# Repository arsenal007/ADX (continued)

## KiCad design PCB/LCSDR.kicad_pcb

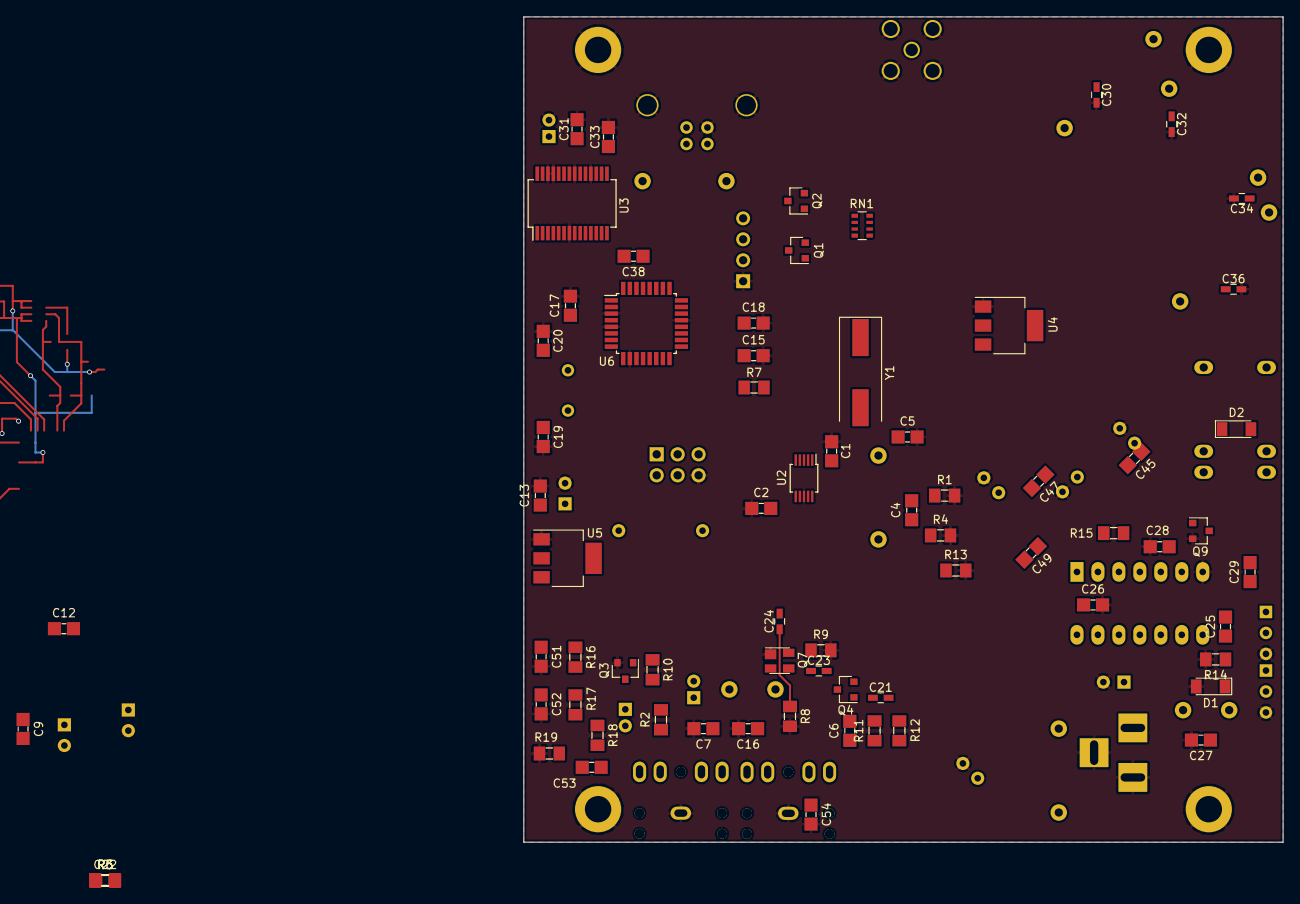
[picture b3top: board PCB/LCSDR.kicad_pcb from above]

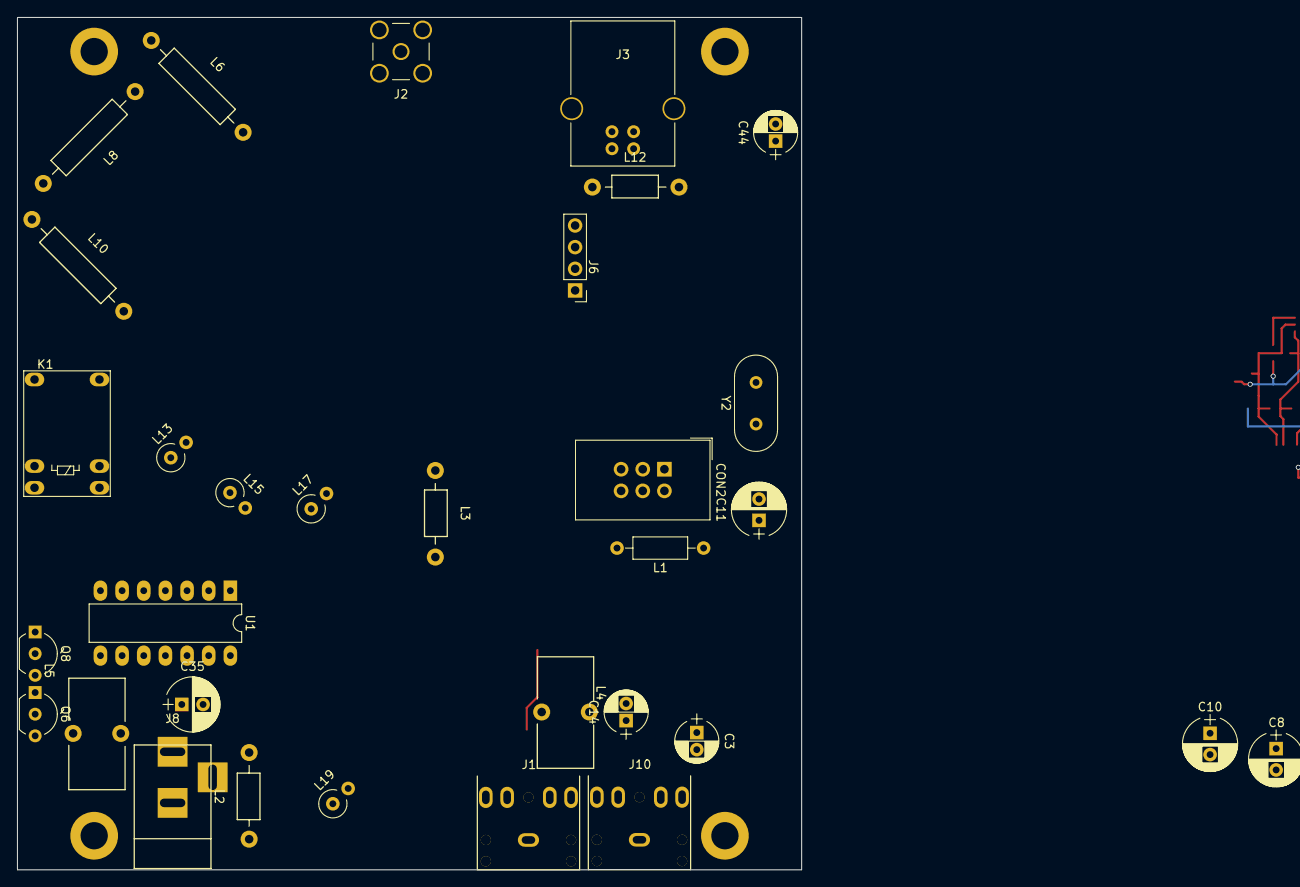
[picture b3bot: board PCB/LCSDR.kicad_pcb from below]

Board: 2 copper layers, 92.0 x 100.0 mm, 108 parts (32 on the bottom side), 61 nets.

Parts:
C1, C2: 1µF; C_1206_0603
C3, C14: 2.2uF; CP_Radial_D5.0mm_P2.00mm
C4, C5, C6, C7, C9, C12, C13, C15, C16, C17, C18, C22, C25, C26, C29, C31, C33, C38, C53, C54: 100nF; C_1206_0603
C8, C10, C11, C35: 100uF; CP_Radial_D6.3mm_P2.50mm
C19, C20: 22pF; C_1206_0603
C21, C23, C24: 10nF; C_0603_HandSoldering
C27, C28: 100pF; C_1206_0603
C30, C36: 270pF; C_0603_HandSoldering
C32, C34: 680pF; C_0603_HandSoldering
C44: 10uF; CP_Radial_D5.0mm_P2.00mm
C45, C49: 330pF; C_1206_0603
C47: 220pF; C_1206_0603
C51, C52: 10nF; C_1206_0603
CON2: AVR-ISP-6; IDC-Header_2x03_Pitch2.54mm_Straight
D1, D2: LL4148; D_MiniMELF
J1: MIC; audio_jack_3_5mm_PJ307
J2: ANT; SMA_THT_Jack_Straight
J3: USB_B
J6: I2C; Pin_Header_Straight_1x04_Pitch2.54mm
J8: Jack-DC; BARREL_JACK
J10: SPK; audio_jack_3_5mm_PJ307
J12, J13, J14, J15: Conn_01x01; MountingHole_3.2mm_M3_DIN965_Pad
K1: TIANBO-HJR-4102-L; Relay_SPDT_HJR-4102
L1: 100uH; R_Axial_DIN0207_L6.3mm_D2.5mm_P10.16mm_Horizontal
L2: 33µH; Choke_Horizontal_RM10mm
L3: 4.7uH; Choke_Horizontal_RM10mm
L4: 100mH; Choke_Toroid_6,5x13mm_Vertical
L5: 20uH; Choke_Toroid_6,5x13mm_Vertical
L6, L10: 1.32uH; Choke_Horizontal_RM15mm
L8: 1.72uH; Choke_Horizontal_RM15mm
L12: 10uH; Choke_Horizontal_RM10mm
L13, L19: 1uH; R_Axial_DIN0309_L9.0mm_D3.2mm_P2.54mm_Vertical
L15, L17: 680nH; R_Axial_DIN0309_L9.0mm_D3.2mm_P2.54mm_Vertical
Q1, Q2: 2N7002; SOT-23
Q3: BC847; SOT-23
Q4: BFR93A; SOT-23
Q6, Q8: BS170; TO-92_Inline_Wide
Q7: BF998; SOT-143
Q9: BC849; SOT-23
R1: 4R7; R_1206_0603
R2: 3.9K; R_1206_0603
R3, R5: 100; R_1206_0603
R4: 47R; R_1206_0603
R6: 2.2k; R_1206_0603
R7, R16, R17: 10k; R_1206_0603
R8, R12: 470; R_1206_0603
R9: 27k; R_1206_0603
R10: 470k; R_1206_0603
R11: 2.7k; R_1206_0603
R13: 1k; R_1206_0603
R14: 2.7K; R_1206_0603
R15: 3.3k; R_1206_0603
R18: 1M; R_1206_0603
R19: 4.7K; R_1206_0603
RN1: 10k; R_Array_Convex_4x0603
U1: 74AC14; DIP-14_W7.62mm_LongPads
U2: Si5351; MSOP-10_3x3mm_Pitch0.5mm
U3: FT232RL; SSOP-28_5.3x10.2mm_Pitch0.65mm
U4: LM1117-5.0; SOT-223-3_TabPin2
U5: LM1117-3.3; SOT-223-3_TabPin2
U6: ATMEGA328P-AU; TQFP-32_7x7mm_Pitch0.8mm
Y1: 25Mhz; Crystal_SMD_HC49-SD
Y2: 20Mhz; Crystal_HC49-U_Vertical

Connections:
+3V3: C1.1, C11.1, C13.1, L1.1, Q1.1, Q2.1, R18.1, RN1.5, RN1.6, U2.1, U5.2
+5V: C10.1, C12.1, C15.1, C17.1, C26.1, CON2.2, J6.2, L12.1, R7.1, RN1.7, RN1.8, U1.14, U4.2, U5.3, U6.4, U6.6, U6.18
+12V: C8.1, C9.1, D2.1, K1.8, L2.1, R2.1, R3.2, R5.2, U4.3
+12VA: C35.1, J8.1, L2.2, L5.1
CLK1: C24.2, U2.9
CLK2: U1.1, U1.3, U1.5, U1.9, U1.11, U1.13, U2.6
GND: C1.2, C2.1, C5.2, C7.2, C8.2, C9.2, C10.2, C11.2, C12.2, C13.2, C15.2, C16.2, C17.2, C18.2, C19.2, C20.2, C22.2, C26.2, C27.2, C28.2, C30.2, C31.2, C32.2, C33.2, C34.2, C35.2, C36.2, C44.2, C51.2, C52.2, C54.2, CON2.6, D1.2, J1.1, J2.2, J3.4, J3.5, J6.1, J8.2, J8.3, J10.1, J12.1, J13.1, J14.1, J15.1, L13.2, L15.2, L17.2, L19.2, Q3.2, Q6.3, Q7.1, Q8.3, Q9.2, R1.2, R4.2, R8.2, R9.2, R13.2, R14.2, R19.2, U1.7, U2.8, U3.7, U3.18, U3.21, U3.25, U3.26, U4.1, U5.1, U6.3, U6.5, U6.10, U6.21
IO_5: U6.1, U6.2
LPF: C36.1, K1.1, K1.12, L10.2
unnamed: C2.2, L1.2, U2.7
unnamed: C3.1, Q3.3, R2.2, R10.2
unnamed: C3.2, C54.1, J1.2, J1.3, J1.4, J1.5
unnamed: C4.1, Q4.2, R4.1
unnamed: C4.2, R1.1
unnamed: C5.1, L3.1, R3.1
unnamed: C6.1, R11.1, R12.1
unnamed: C7.1, C14.1, L4.1
unnamed: C14.2, Q3.1, R10.1
unnamed: C16.1, L4.2, Q7.2, R6.1
unnamed: C18.1, U6.20
unnamed: C19.1, U6.8, Y2.1
unnamed: C20.1, U6.7, Y2.2
unnamed: C21.1, Q4.1, R12.2, R13.1
unnamed: C22.1, R5.1, R6.2
unnamed: C23.1, Q7.4, R9.1
unnamed: C24.1, Q7.3, R8.1
unnamed: C25.1, U1.2, U1.4, U1.6, U1.8, U1.10, U1.12
unnamed: C25.2, D1.1, Q6.2, Q8.2, R14.1
unnamed: C27.1, C29.1, L5.2, Q6.1, Q8.1
unnamed: C28.1, Q9.1, R15.1
unnamed: C29.2, K1.6
unnamed: C30.1, J2.1, L6.1
unnamed: C31.1, C44.1, L12.2, U3.4, U3.19, U3.20
unnamed: C32.1, L6.2, L8.1
unnamed: C33.1, U3.17
unnamed: C34.1, L8.2, L10.1
unnamed: C38.2, U3.2
unnamed: C45.2, C47.1, L15.1
unnamed: C47.2, C49.1, L17.1
unnamed: C51.1, R16.1, U6.11
unnamed: C52.1, R16.2, R17.1
unnamed: C53.1, J10.2, J10.3, J10.4, J10.5
unnamed: C53.2, R17.2, R18.2, R19.1
unnamed: CON2.1, U6.16
unnamed: CON2.3, U6.17
unnamed: CON2.4, U6.15
unnamed: D2.2, K1.5, Q9.3
unnamed: J3.2, U3.15
unnamed: J3.3, U3.16
unnamed: Q1.2, RN1.4, U2.5
unnamed: Q2.2, RN1.3, U2.4
unnamed: U2.2, Y1.2
unnamed: U2.3, Y1.1
PREAMP_IN: C21.2, C49.2, L19.1
PREAMP_OUT: C6.2, C23.2, L3.2, Q4.3, R11.2
RESET: C38.1, CON2.5, R7.2, U6.29
RF_IN: C45.1, K1.7, L13.1
RxD: U3.1, U6.30
SCL: J6.4, Q2.3, RN1.1, U6.28
SDA: J6.3, Q1.3, RN1.2, U6.27
TxD: U3.5, U6.31

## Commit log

2022-08-31 PCBs_Opa with axial inductace in HPF
2022-09-02 operational amplifier Direct detection receiver
2022-09-11 add LPF/HPF RFSimm models
2022-09-18 release gerber files
2022-09-18 add text to HPF/LPF sch
2022-10-11 ADX988 CAT: add FE, FI commands
2022-11-03 add PCB changes
2022-11-03 add INIT sketch, not tested yet
2022-11-27 discret, simple, CH340E
2022-12-18 INIT project, si5351 generate properly frequency
2022-12-25 add printout, finish PCB, add LM7805
2022-12-26 greber files
2023-01-05 Arduino Nano PCB ADX988 DSP
2023-01-15 migrate to attiny1614
2023-01-30 Migrate to LGT8F328p
2023-01-31 try to fix detector
